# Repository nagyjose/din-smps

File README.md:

# DIN-Rail Switched-Mode Power Supply (`din-smps`)

> Highly reliable, galvanically isolated offline flyback power supply designed for standard DIN-rail modular enclosures, powering home automation controllers and bus peripherals.

**Project Status:** `Completed / Production Ready` | **EDA Tool:** `Autodesk Eagle 9.x` | **Category:** `Power Electronics / Hardware`

---

## 1. Overview and Purpose

The `din-smps` repository provides an offline AC/DC switched-mode power supply (SMPS) engineered specifically to fit standard 35 mm DIN-rail modular enclosures (such as the **Kradex Z106J** series). The power supply converts wide-range AC mains (85–265 V AC, 50/60 Hz) into stable, clean, galvanically isolated DC voltages required by modular home automation equipment, relay drivers, microcontrollers, and communication transceivers.

### Key Features
- **Galvanic Isolation:** Primary-to-secondary isolation exceeding 3 kV via an optocoupler feedback loop and specialized flyback transformer.
- **High Efficiency & Low Standby:** Powered by the **Power Integrations TNY267PN** TinySwitch-II offline switcher with EcoSmart® technology, providing auto-restart, cycle skipping, and thermal shutdown.
- **Robust Mains Protection:** Multistage input stage incorporating an overcurrent PTC fuse, Metal Oxide Varistor (MOV) surge arrestor, and NTC inrush current limiter.
- **Dual Regulated Output Rails:** Delivers regulated **+12 V DC** (for relay coils, RS-485 bus line, and actuators) and **+5 V DC** (for digital logic and microcontrollers).
- **CAD & Mechanical Enclosure Ready:** Includes board layout, schematic, CAM drill legends, and exact mechanical DXF outlines aligned with the Kradex Z106J modular enclosure.

---

## 2. Technical Specifications

| Parameter | Specification (`SMPS-DIN`) |
| :--- | :--- |
| **Input Voltage Range** | 85 – 265 V AC, 50/60 Hz |
| **Primary Topology** | Discontinuous Flyback Converter |
| **Primary Controller IC** | Power Integrations TNY267PN |
| **Transformer** | Myrra 74080 (designed for TinySwitch-II) |
| **Output Voltages** | **+12 V DC** (Regulated) & **+5 V DC** (Regulated) |
| **Linear Post-Regulators** | STMicroelectronics L7812ABV & L7805ACV |
| **Output Rectifier** | 1N5822 (3 A / 40 V Schottky Barrier Rectifier) |
| **Feedback Loop** | Sharp PC817 optocoupler + 15V Zener diode reference |
| **Input Protection** | PTC Resettable Fuse, MOV 680V (HEL-7D681K), NTC 10 Ω |
| **EMI / Safety Filtering** | 2.2 mH filter choke + Y-class ceramic capacitors |
| **Target Enclosure** | Kradex Z106J PS DIN-Rail Modular Box |
| **PCB Form Factor** | Double-sided 1.6 mm FR4, custom enclosure outline |

---

## 3. Architecture & Functional Blocks

The converter follows an offline flyback architecture with secondary linear post-regulation for ultra-low noise:

```mermaid
flowchart TD
    subgraph AC_Input["Mains AC Input Stage"]
        AC["230V AC Mains (L, N, PE)"] --> PROT["Protection<br/>(PTC Fuse + MOV HEL-7D681K + NTC 10R)"]
        PROT --> RECT["Full-Bridge Rectifier<br/>(4x 1N4005)"]
        RECT --> DC_BUS["DC Bus & Filter<br/>(Pi-Filter: 2x 3.3µF / 400V + 2.2mH L1)"]
    end

    subgraph Primary_Flyback["Galvanically Isolated Flyback Converter"]
        DC_BUS --> TR["Flyback Transformer<br/>(Myrra 74080)"]
        DC_BUS --> RCD["RCD Snubber<br/>(1N4005 + 2MΩ / 100kΩ + 2.2nF)"]
        RCD --> TR
        TR <--> TNY["Flyback Switcher IC<br/>(Power Integrations TNY267PN)"]
    end

    subgraph Secondary_Output["Secondary Rectification & Regulation"]
        TR --> SCHOTTKY["Secondary Rectifier<br/>(1N5822 Schottky 3A)"]
        SCHOTTKY --> SEC_FILT["Bulk Filtering<br/>(2x 1000µF + 10µH L2 + 470µF)"]
        SEC_FILT --> REG12["Linear Regulator 12V<br/>(ST L7812ABV)"]
        REG12 --> REG05["Linear Regulator 5V<br/>(ST L7805ACV)"]
        REG12 --> OUT12["+12V DC Output"]
        REG05 --> OUT05["+5V DC Output"]
    end

    subgraph Feedback_Loop["Optocoupler Feedback"]
        SEC_FILT --> ZENER["Voltage Reference<br/>(15V Zener D7 + R5 680Ω)"]
        ZENER --> OPTO["Galvanic Optocoupler<br/>(Sharp PC817)"]
        OPTO -.->|Isolated Feedback Current| TNY
    end

    style AC fill:#e1f5fe,stroke:#0288d1,stroke-width:1.5px
    style TNY fill:#fff3e0,stroke:#f57c00,stroke-width:2px
    style TR fill:#ede7f6,stroke:#512da8,stroke-width:2px
    style OUT12 fill:#e8f5e9,stroke:#388e3c,stroke-width:2px
    style OUT05 fill:#e8f5e9,stroke:#388e3c,stroke-width:2px
```

### Detailed Functional Breakdown
1. **Input Protection & Rectification:**
   - Overcurrent protection via PTC resettable fuse (`FX1`).
   - AC surge absorption via Metal Oxide Varistor (`VAR1`, HEL-7D681K / 420V AC rating).
   - Inrush current limitation at power-up through a 10 Ω NTC thermistor (`TH1`).
   - Full-wave rectification using 1N4005 diodes (`D1`–`D4`) followed by a pi-filter (`C1`, `C2` 3.3 µF / 400V electrolytics and `L1` 2.2 mH choke) to attenuate switching frequencies back into the grid.
2. **Flyback Inversion (TNY267PN):**
   - Incorporates a 700 V power MOSFET, oscillator, high-voltage switched current source, current limit comparator, and thermal shutdown circuitry on a single monolithic IC.
   - Operates in discontinuous conduction mode (DCM) utilizing ON/OFF state control to regulate output voltage with high light-load efficiency.
   - Primary voltage spikes resulting from transformer leakage inductance are clamped by an RCD snubber network (`D5`, `R2`, `R3`, `C4`).
3. **Galvanic Isolation & Feedback Loop:**
   - Output voltage sensing is carried out on the intermediate ~16 V DC rail using a 15 V Zener diode (`D7`) connected in series with the LED emitter of a **Sharp PC817** optocoupler (`IC2`).
   - When the secondary voltage exceeds the Zener threshold (~16.2 V), current conducts through the optocoupler, pulling down the `EN/UV` (Enable/Under-Voltage) pin of the TNY267PN to skip switching cycles.
4. **Post-Regulation Stage:**
   - **+12 V DC Rail:** Regulated by STMicroelectronics `L7812ABV` to supply solid, hum-free DC power for DIN-rail relays, bus transceivers, and external sensors.
   - **+5 V DC Rail:** Cascaded via STMicroelectronics `L7805ACV` for logic circuits, microcontrollers, and Ethernet/CAN controller boards.

---

## 4. Hardware Schematic & Visuals

Below is the full schematic diagram of the dual-output SMPS-DIN converter:

📄 [Open original full-resolution schematic (PDF)](SMPS-DIN.pdf)

---

## 5. Repository Structure

```text
.
├── SMPS-DIN.sch                   # Primary schematic (Autodesk Eagle)
├── SMPS-DIN.brd                   # Primary 2-layer PCB layout (Autodesk Eagle)
├── SMPS-DIN.dxf                   # Mechanical outline and mounting drawing (DXF)
├── SMPS-DIN.pdf                   # Schematic and layout printout
├── DRILEGEND.CFG                  # Eagle drill legend configuration
├── docs/
│   ├── images/                    # Rendered 180 DPI hardware visuals
│   │   └── smps_din_schematic.png # Standard model schematic preview
│   ├── calculations/
│   │   ├── Součástky.xlsx         # Component selection & parameter calculations
│   │   ├── Součástky (version 1).xlsb.xlsx # Early design calculation sheet
│   │   └── order_32668509.csv     # TME procurement order list and parts BOM
│   ├── datasheets/                # Full PDF datasheets for all active & passive parts
│   │   ├── tny263-268g_p.pdf      # Power Integrations TinySwitch-II datasheet
│   │   ├── 74080.pdf              # Myrra 74080 flyback transformer datasheet
│   │   ├── PC817X3NSZ1B.pdf       # Sharp PC817 optocoupler datasheet
│   │   ├── 1N5822-ST.pdf          # ST 1N5822 Schottky diode datasheet
│   │   ├── L78.pdf                # ST L7812 / L7805 linear regulator datasheet
│   │   └── ...                    # Additional component datasheets
│   └── README.md                  # Documentation index
└── README.md                      # Main repository documentation
```

---

## 6. Bill of Materials & Sourcing

The repository includes complete component calculation and procurement files located in [docs/calculations/](file:///c:/Users/josef/Documents/EAGLE/projects/SMPS-DIN/docs/calculations).

### Core Components Summary

| Designator | Component / Part Number | Manufacturer | Package / Footprint | Description |
| :--- | :--- | :--- | :--- | :--- |
| `IC1` | **TNY267PN** | Power Integrations | DIP-8B | TinySwitch-II offline flyback switcher IC |
| `IC2` | **PC817X4NSZ1B** | Sharp | DIP-4 | Galvanic isolation optocoupler |
| `IC3` | **L7812ABV** | STMicroelectronics | TO-220 | Linear positive voltage regulator (+12 V, 1 A) |
| `IC4` | **L7805ACV** | STMicroelectronics | TO-220 | Linear positive voltage regulator (+5 V, 1 A) *(Standard only)* |
| `TR1` | **74080** | Myrra | PCB Mount | Flyback transformer (optimized for TNY series) |
| `D1–D4, D5` | **1N4005** | Diotec | DO-41 (Vertical) | 600 V / 1 A silicon rectifiers |
| `D6` | **1N5822** | STMicroelectronics | DO-201AD | 40 V / 3 A Schottky barrier rectifier diode |
| `D7` | **BZX55C15** | Vishay / CDIL | DO-35 | 15 V / 0.5 W Zener voltage reference diode |
| `VAR1` | **HEL-7D681K** | SR Passives | Radial Disk 7 mm | Metal Oxide Varistor (420 V AC continuous) |
| `TH1` | **NTCS-10-10-2** | SR Passives | Radial Disk | 10 Ω NTC inrush current limiter *(Standard only)* |
| `FX1` | **FX100-30** | ECE | Radial | Resettable PTC fuse (with PTF/77 holder) |
| `L1` | **COIL1010-2.2** | Ferrocore | Radial Choke | 2.2 mH power inductor (input Pi-filter) |
| `L2` | **COIL0608-0.01** | Ferrocore | Radial Choke | 10 µH power inductor (secondary filter) |
| `C1, C2` | **ECA2GM3R3B** | Panasonic | Radial Ø10 mm | 3.3 µF / 400 V DC electrolytic capacitor |
| `C8, C9` | **EWH1EK102G20OT** | Aishi | Radial Ø10 mm | 1000 µF / 25 V low-ESR electrolytic capacitor |
| `C10` | **PF1V471MNN1020** | Elite | Radial Ø10 mm | 470 µF / 35 V low-ESR electrolytic capacitor |
| `CON1` | **XY301V-3P+ (5.00)** | Xinya | 5.00 mm Pitch | 3-position screw terminal block (AC Mains) |
| `CON2` | **XY301V-3P+ (5.00)** | Xinya | 5.00 mm Pitch | 3-position screw terminal block (DC Outputs) |
| `ENCL` | **Z106J PS** | Kradex | Modular Box | DIN-rail enclosure (see `SMPS-DIN.dxf`) |

---

## 7. Manufacturing & EDA Guidelines

### Opening and Editing in Autodesk Eagle
1. Open Autodesk Eagle (version 8.x, 9.x, or Autodesk Fusion 360 Electronics).
2. Open project:
   - For standard version: open `SMPS-DIN.sch` / `SMPS-DIN.brd`.
   - For compact version: open `variants/smps-din-lite/SMPS-DIN-LITE.sch` / `SMPS-DIN-LITE.brd`.
3. To generate Gerber / drill files for PCB production, load standard 2-layer CAM job and apply `DRILEGEND.CFG`.

### Safety and High-Voltage Notice
> [!WARNING]
> This circuit is directly connected to hazardous 230 V AC mains voltage! High voltages up to ~400 V DC are present across `C1`, `C2`, and the primary side of `TR1` during operation and for some time after disconnection.
> - Ensure appropriate creepage and clearance distances (> 6.0 mm) between primary and secondary copper traces.
> - Always bench-test using an isolating transformer and current-limited mains supply.
> - Install within a certified insulating DIN enclosure (e.g. Kradex Z106J) before connecting to mains.

---

## 8. Cross-Project Relationships & Ecosystem

This project is an integral building block of the **Smart Home DIN-Rail Ecosystem**:
- **[din-smps-lite](https://github.com/nagyjose/din-smps-lite):** Space-optimized single-rail (+12 V) DIN power supply variant for auxiliary racks.
- **[din-control-module](https://github.com/nagyjose/din-control-module):** Main DIN-rail central automation unit, powered by the +12V / +5V rails from this supply.
- **[din-relay-module](https://github.com/nagyjose/din-relay-module):** DIN-rail 8-channel power relay actuator module, drawing coil power from the +12V rail.
- **[domovni-rozvadec-dokumentace](https://github.com/nagyjose/domovni-rozvadec-dokumentace):** Cabinet wiring diagrams and schematics showing installation of this SMPS alongside the Wattrouter controller.

---

## 9. License

This hardware project is open source and licensed under the [MIT License](LICENSE) (or CERN Open Hardware Licence v2 - Permissive).

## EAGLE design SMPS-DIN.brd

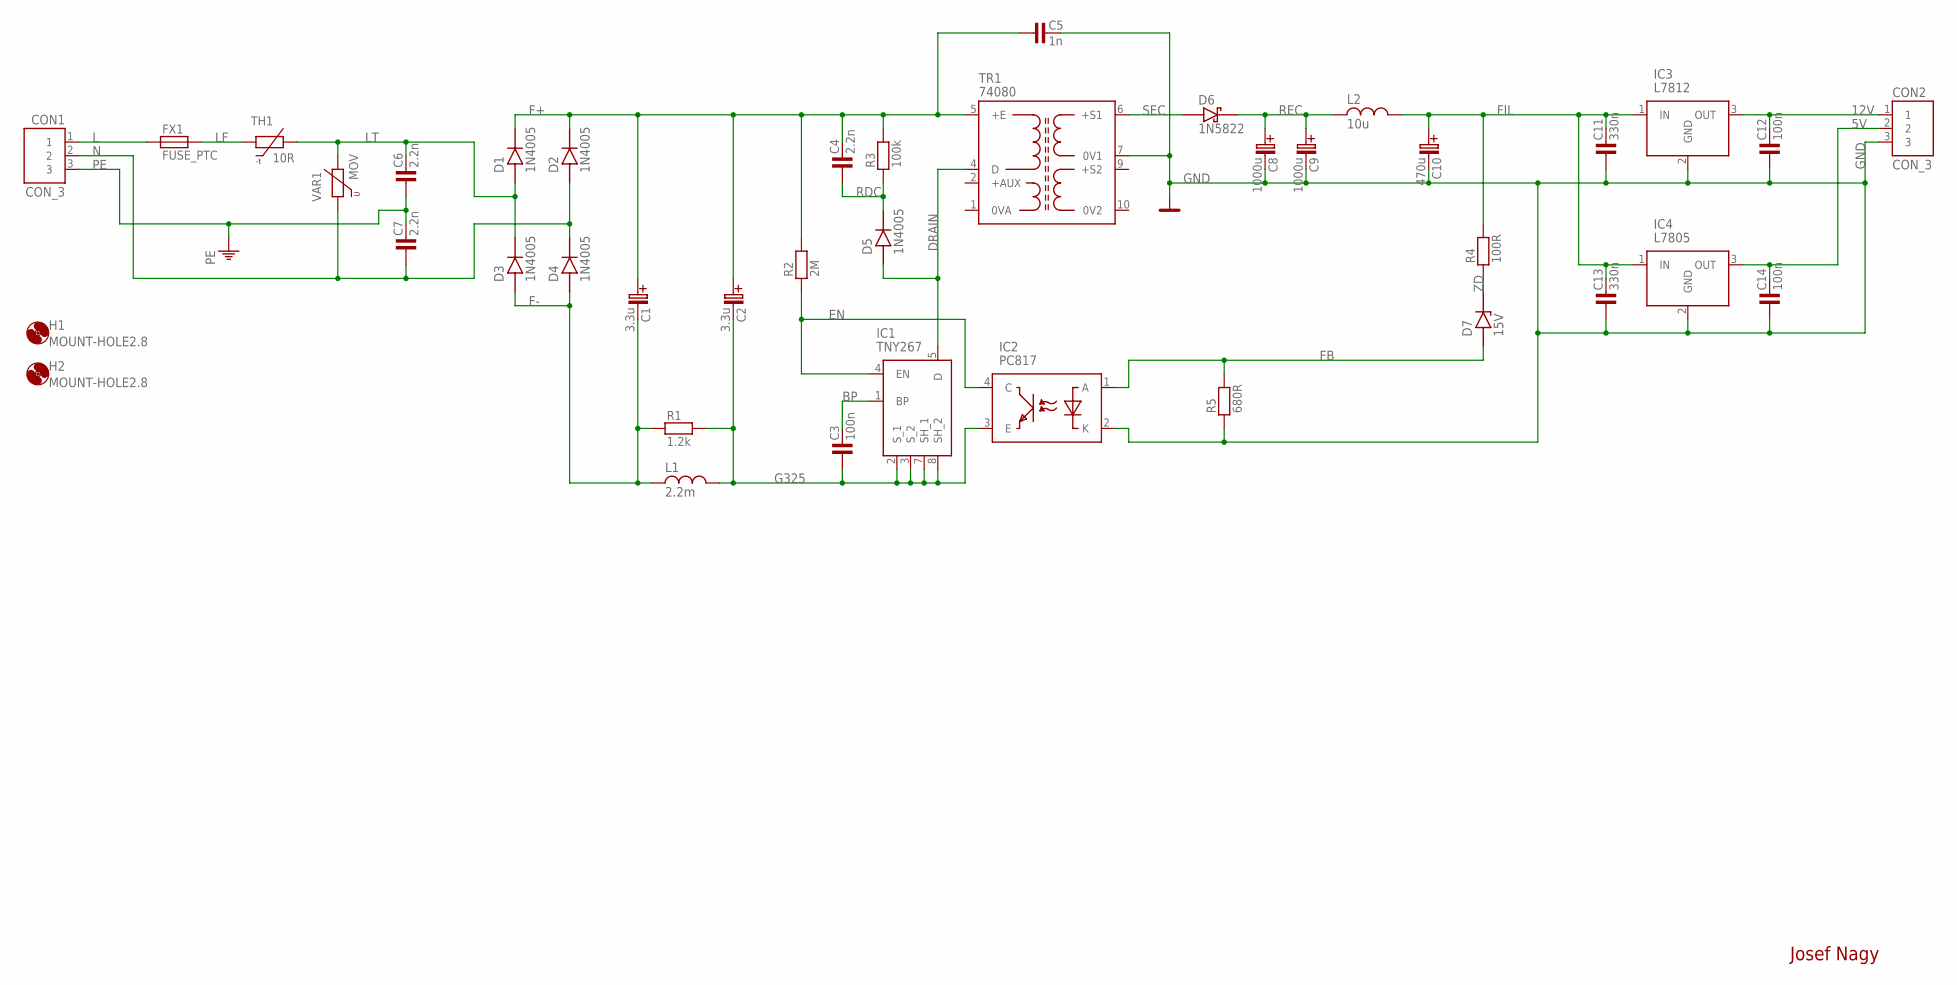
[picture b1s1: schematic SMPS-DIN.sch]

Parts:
C1, C2: 3.3u; C-EL_5
C3: 100n; C-10
C4, C6, C7: 2.2n; C-10
C5: 1n; C-10
C8, C9: 1000u; C-EL_5
C10: 470u; C-EL_5
C11, C13: 330n; C-5
C12, C14: 100n; C-2,5
CON1, CON2: CON_3; CON3
D1, D2, D3, D4, D5: 1N4005; DO41_V
D6: 1N5822; DO201_V
D7: 15V; DO35
FX1: FUSE_PTC
H1, H2: MOUNT-HOLE2.8; 2,8
IC1: TNY267; P-PACKAGE(DIP-8B)_1
IC2: PC817; DIP762W60P254L460H455Q4N
IC3: L7812; TO255P460X1020X2008-3P
IC4: L7805; TO255P460X1020X2008-3P
L1: 2.2m; L-5
L2: 10u; L-3
R1: 1.2k; R-7,5
R2: 2M; R-STOJ2
R3: 100k; R-7,5
R4: 100R; R-7,5
R5: 680R; R-7,5
TH1: 10R; THERMISTOR
TR1: 74080
VAR1: MOV; MOV_VARISTOR

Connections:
5V: C14.2, CON2.2, IC4.3 (OUT)
12V: C12.2, CON2.1, IC3.3 (OUT)
BP: C3.2, IC1.1 (BP)
DRAIN: D5.A, IC1.5 (D), TR1.4 (D)
EN: IC1.4 (EN), IC2.4 (C), R2.1
F+: C1.C+ (C_EL+), C2.C+ (C_EL+), C4.2, C5.1, D1.K (C), D2.K (C), R2.2, R3.2, TR1.5 (+E)
F-: C1.C- (C_EL-), D3.A, D4.A, L1.1, R1.1
FB: D7.A, IC2.1 (A), R5.2
FIL: C10.C+ (C_EL+), C11.2, C13.2, IC3.1 (IN), IC4.1 (IN), L2.2, R4.2
G325: C2.C- (C_EL-), C3.1, IC1.2 (S_1), IC1.3 (S_2), IC1.7 (SH_1), IC1.8 (SH_2), IC2.3 (E), L1.2, R1.2
GND: C5.2, C8.C- (C_EL-), C9.C- (C_EL-), C10.C- (C_EL-), C11.1, C12.1, C13.1, C14.1, CON2.3, IC2.2 (K), IC3.2 (GND), IC4.2 (GND), R5.1, TR1.7 (0V1)
L: CON1.1, FX1.1
LF: FX1.2, TH1.1
LT: C6.2, D1.A, D3.K (C), TH1.2, VAR1.2
N: C7.1, CON1.2, D2.A, D4.K (C), VAR1.1
PE: C6.1, C7.2, CON1.3
RDC: C4.1, D5.K (C), R3.1
REC: C8.C+ (C_EL+), C9.C+ (C_EL+), D6.K (C), L2.1
SEC: D6.A, TR1.6 (+S1)
ZD: D7.K (C), R4.1

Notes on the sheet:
Josef Nagy

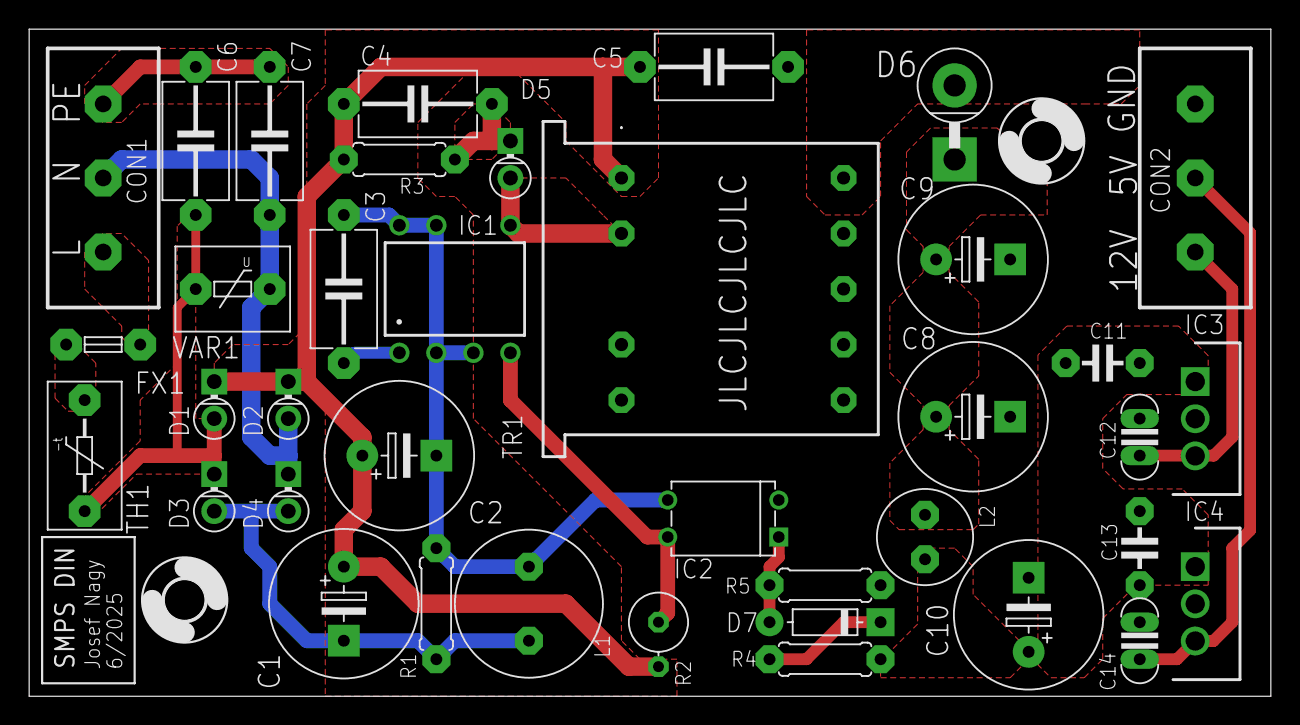
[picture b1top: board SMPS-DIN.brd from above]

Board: 2 copper layers, 85.2 x 45.8 mm, 40 parts (0 on the bottom side), 20 nets.
